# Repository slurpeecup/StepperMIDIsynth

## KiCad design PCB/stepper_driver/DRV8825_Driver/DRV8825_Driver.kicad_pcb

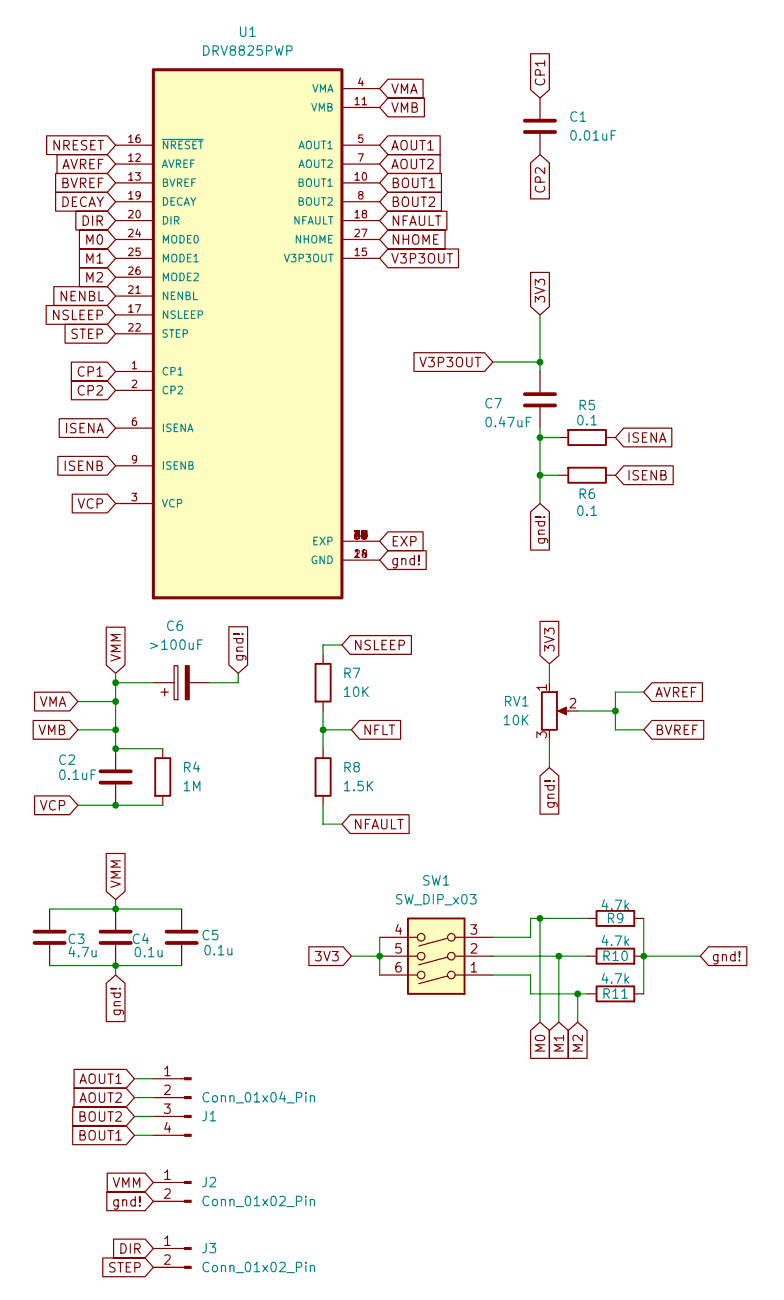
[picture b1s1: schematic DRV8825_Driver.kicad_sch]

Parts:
C1: 0.01uF; C_0603_1608Metric
C2: 0.1uF; C_0603_1608Metric
C3: 4.7u; C_0603_1608Metric
C4, C5: 0.1u; C_0603_1608Metric
C6: >100uF; CP_Elec_10x10
C7: 0.47uF; C_0603_1608Metric
J1: Conn_01x04_Pin; JST_XH_B4B-XH-A_1x04_P2.50mm_Vertical
J2: Conn_01x02_Pin; TerminalBlock_4Ucon_1x02_P3.50mm_Horizontal
J3: Conn_01x02_Pin; JST_XH_B2B-XH-A_1x02_P2.50mm_Vertical
R4: 1M; R_0603_1608Metric
R5, R6: 0.1; R_0603_1608Metric
R7: 10K; R_0603_1608Metric
R8: 1.5K; R_0603_1608Metric
R9, R10, R11: 4.7k; R_0603_1608Metric
RV1: 10K; Bourns_Trimpot_3.8x3.6
SW1: SW_DIP_x03; CONNFLY DIP-3
U1: DRV8825PWP; IC_TPS61196PWPRQ1

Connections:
3V3: C7.1, RV1.1, SW1.4, SW1.5, SW1.6, U1.15 (V3P3OUT)
AOUT1: J1.1, U1.5 (AOUT1)
AOUT2: J1.2, U1.7 (AOUT2)
AVREF: RV1.2, U1.12 (AVREF), U1.13 (BVREF)
BOUT1: J1.4, U1.10 (BOUT1)
BOUT2: J1.3, U1.8 (BOUT2)
CP1: C1.1, U1.1 (CP1)
CP2: C1.2, U1.2 (CP2)
DECAY: U1.19 (DECAY)
DIR: J3.1, U1.20 (DIR)
EXP: U1.29 (EXP), U1.30 (EXP), U1.31 (EXP), U1.32 (EXP), U1.33 (EXP), U1.34 (EXP), U1.35 (EXP), U1.36 (EXP), U1.37 (EXP), U1.38 (EXP), U1.39 (EXP), U1.40 (EXP), U1.41 (EXP), U1.42 (EXP), U1.43 (EXP), U1.44 (EXP), U1.45 (EXP), U1.46 (EXP), U1.47 (EXP), U1.48 (EXP), U1.49 (EXP), U1.50 (EXP)
ISENA: R5.1, U1.6 (ISENA)
ISENB: R6.1, U1.9 (ISENB)
M0: R9.1, SW1.3, U1.24 (MODE0)
M1: R10.1, SW1.2, U1.25 (MODE1)
M2: R11.1, SW1.1, U1.26 (MODE2)
NENBL: U1.21 (NENBL)
NFAULT: R8.2, U1.18 (NFAULT)
NFLT: R7.2, R8.1
NHOME: U1.27 (NHOME)
NRESET: U1.16 (~NRESET)
NSLEEP: R7.1, U1.17 (NSLEEP)
STEP: J3.2, U1.22 (STEP)
VCP: C2.2, R4.2, U1.3 (VCP)
VMA: C2.1, C3.1, C4.1, C5.1, C6.1, J2.1, R4.1, U1.4 (VMA), U1.11 (VMB)
gnd!: C3.2, C4.2, C5.2, C6.2, C7.2, J2.2, R5.2, R6.2, R9.2, R10.2, R11.2, RV1.3, U1.14 (GND), U1.28 (GND)

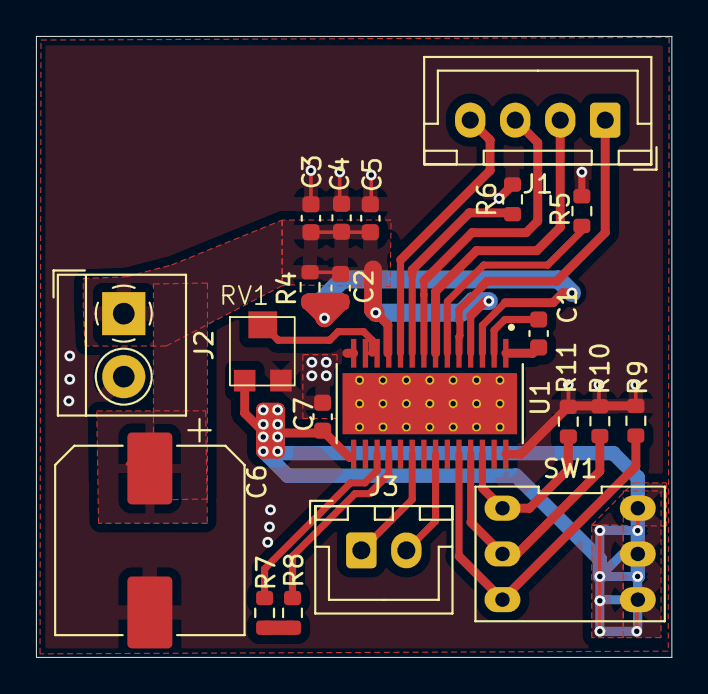
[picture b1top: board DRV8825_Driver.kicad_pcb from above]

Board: 2 copper layers, 35.3 x 34.5 mm, 21 parts (0 on the bottom side), 22 nets.

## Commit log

2024-06-25 single_driver_rev1
2024-06-25 footprint reduction
2026-02-23 blah
